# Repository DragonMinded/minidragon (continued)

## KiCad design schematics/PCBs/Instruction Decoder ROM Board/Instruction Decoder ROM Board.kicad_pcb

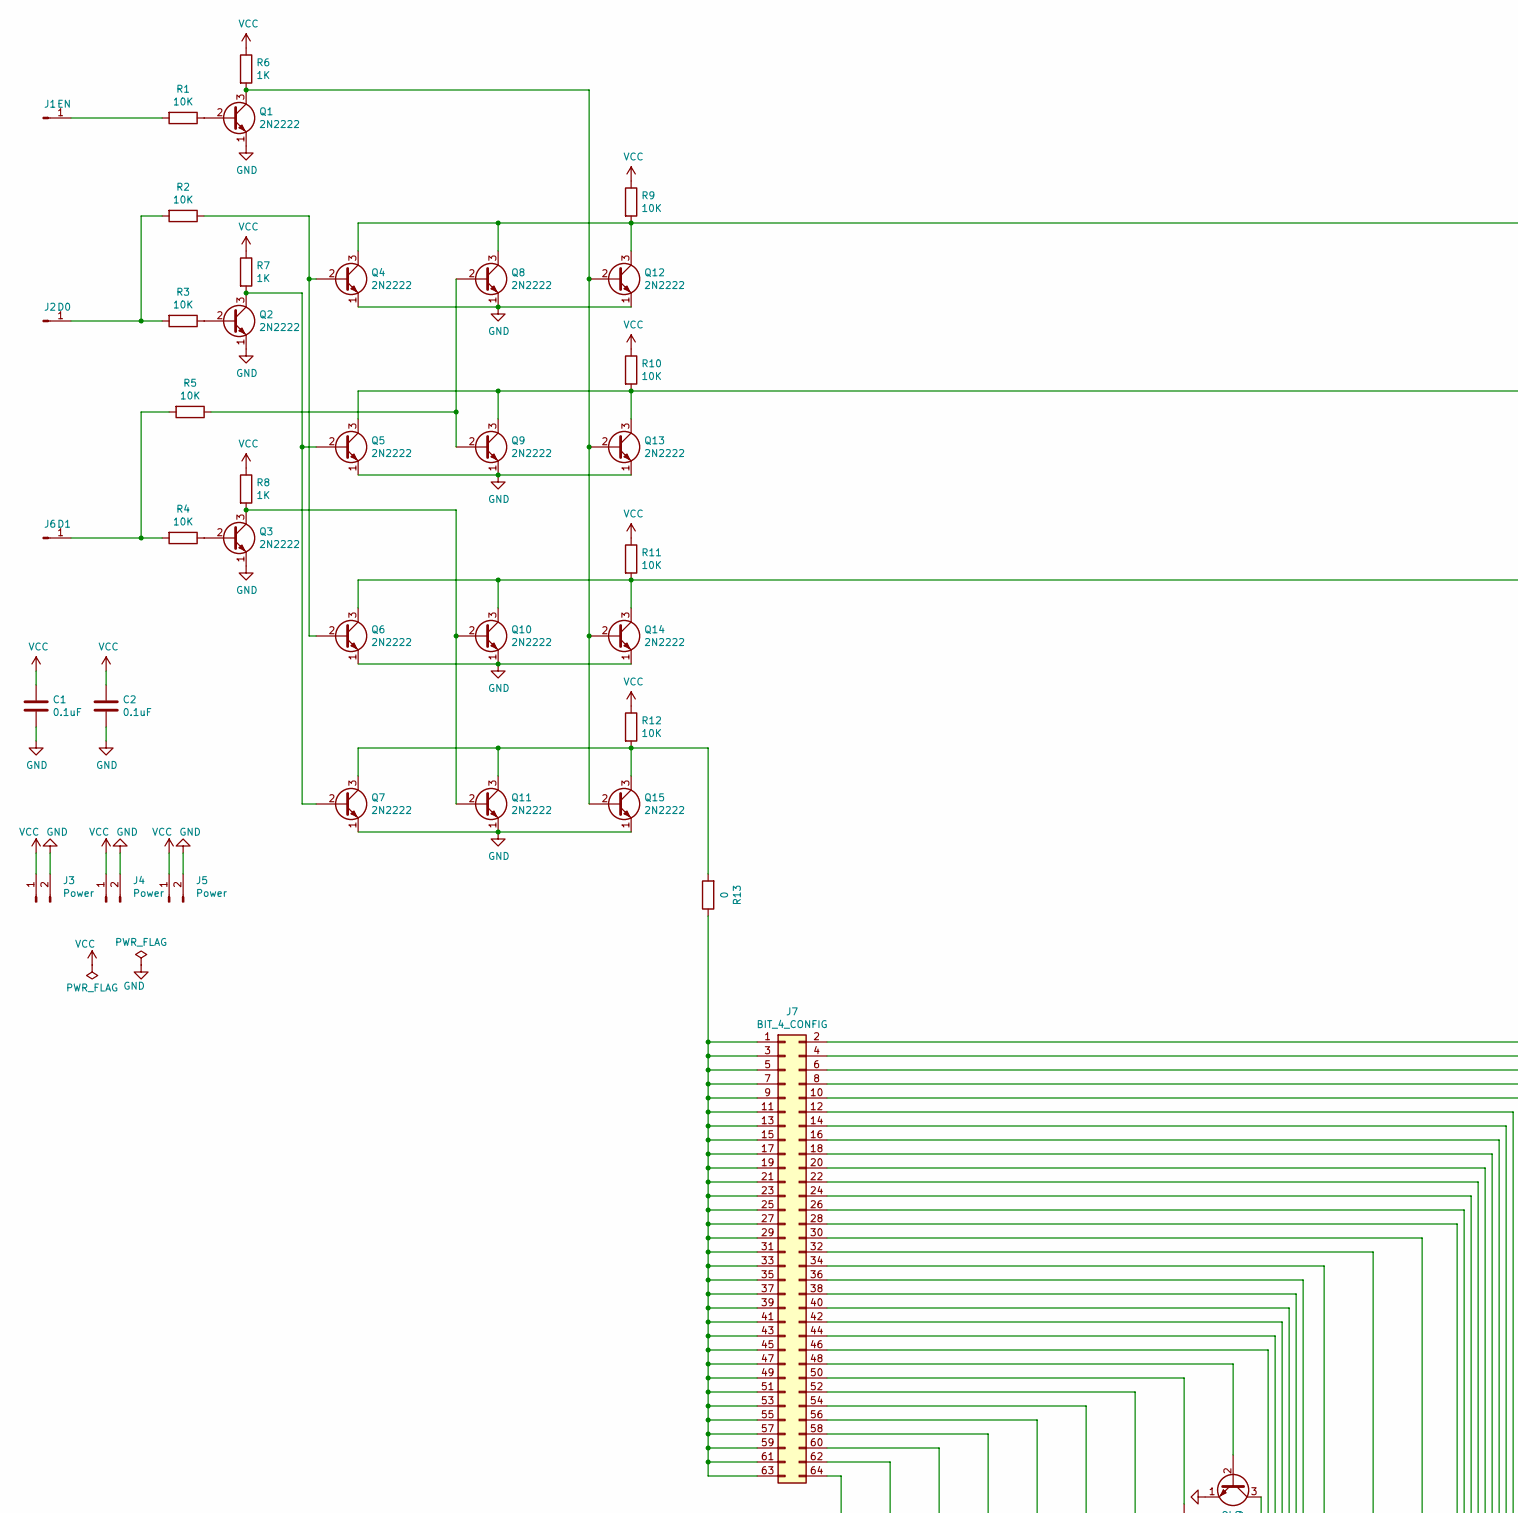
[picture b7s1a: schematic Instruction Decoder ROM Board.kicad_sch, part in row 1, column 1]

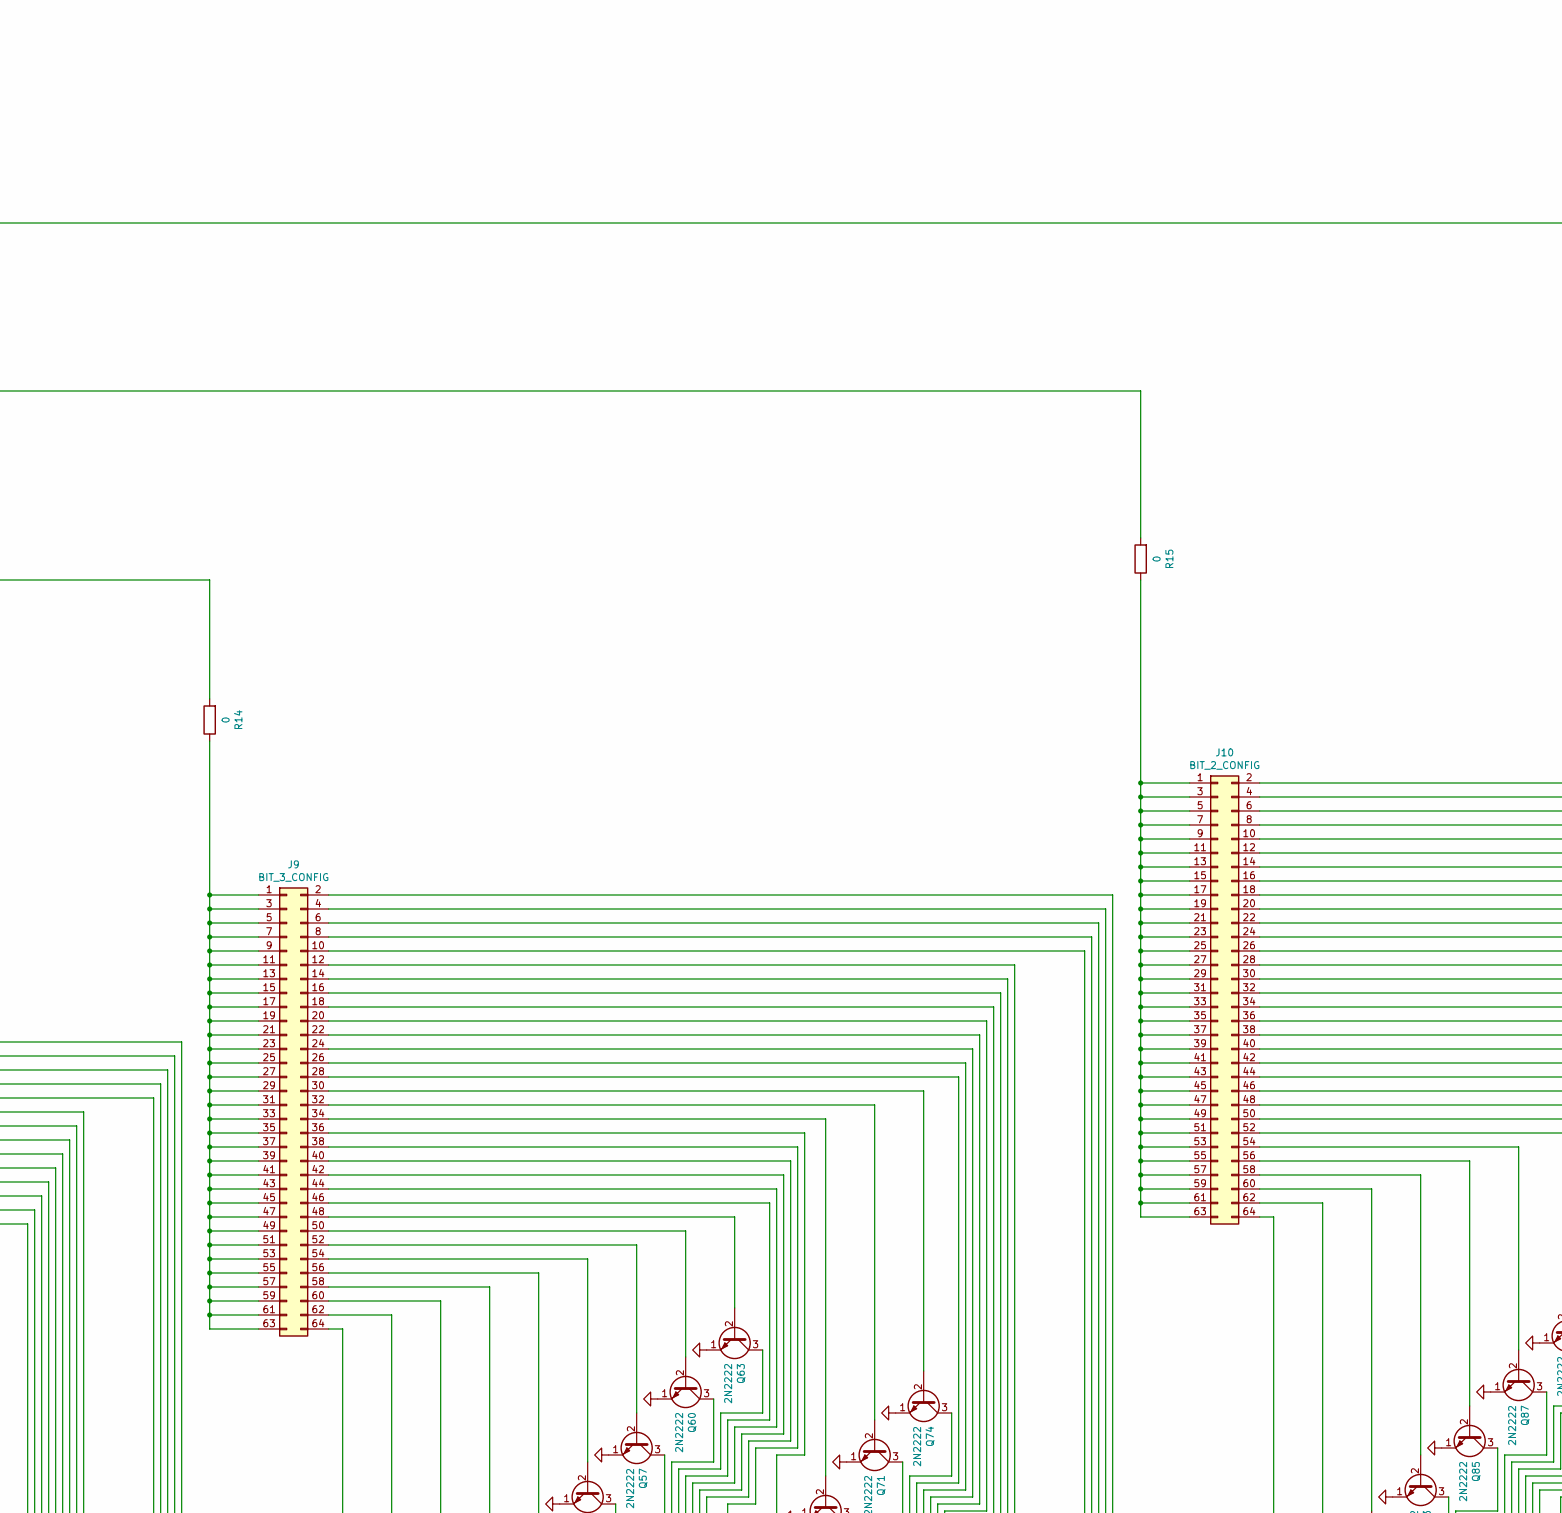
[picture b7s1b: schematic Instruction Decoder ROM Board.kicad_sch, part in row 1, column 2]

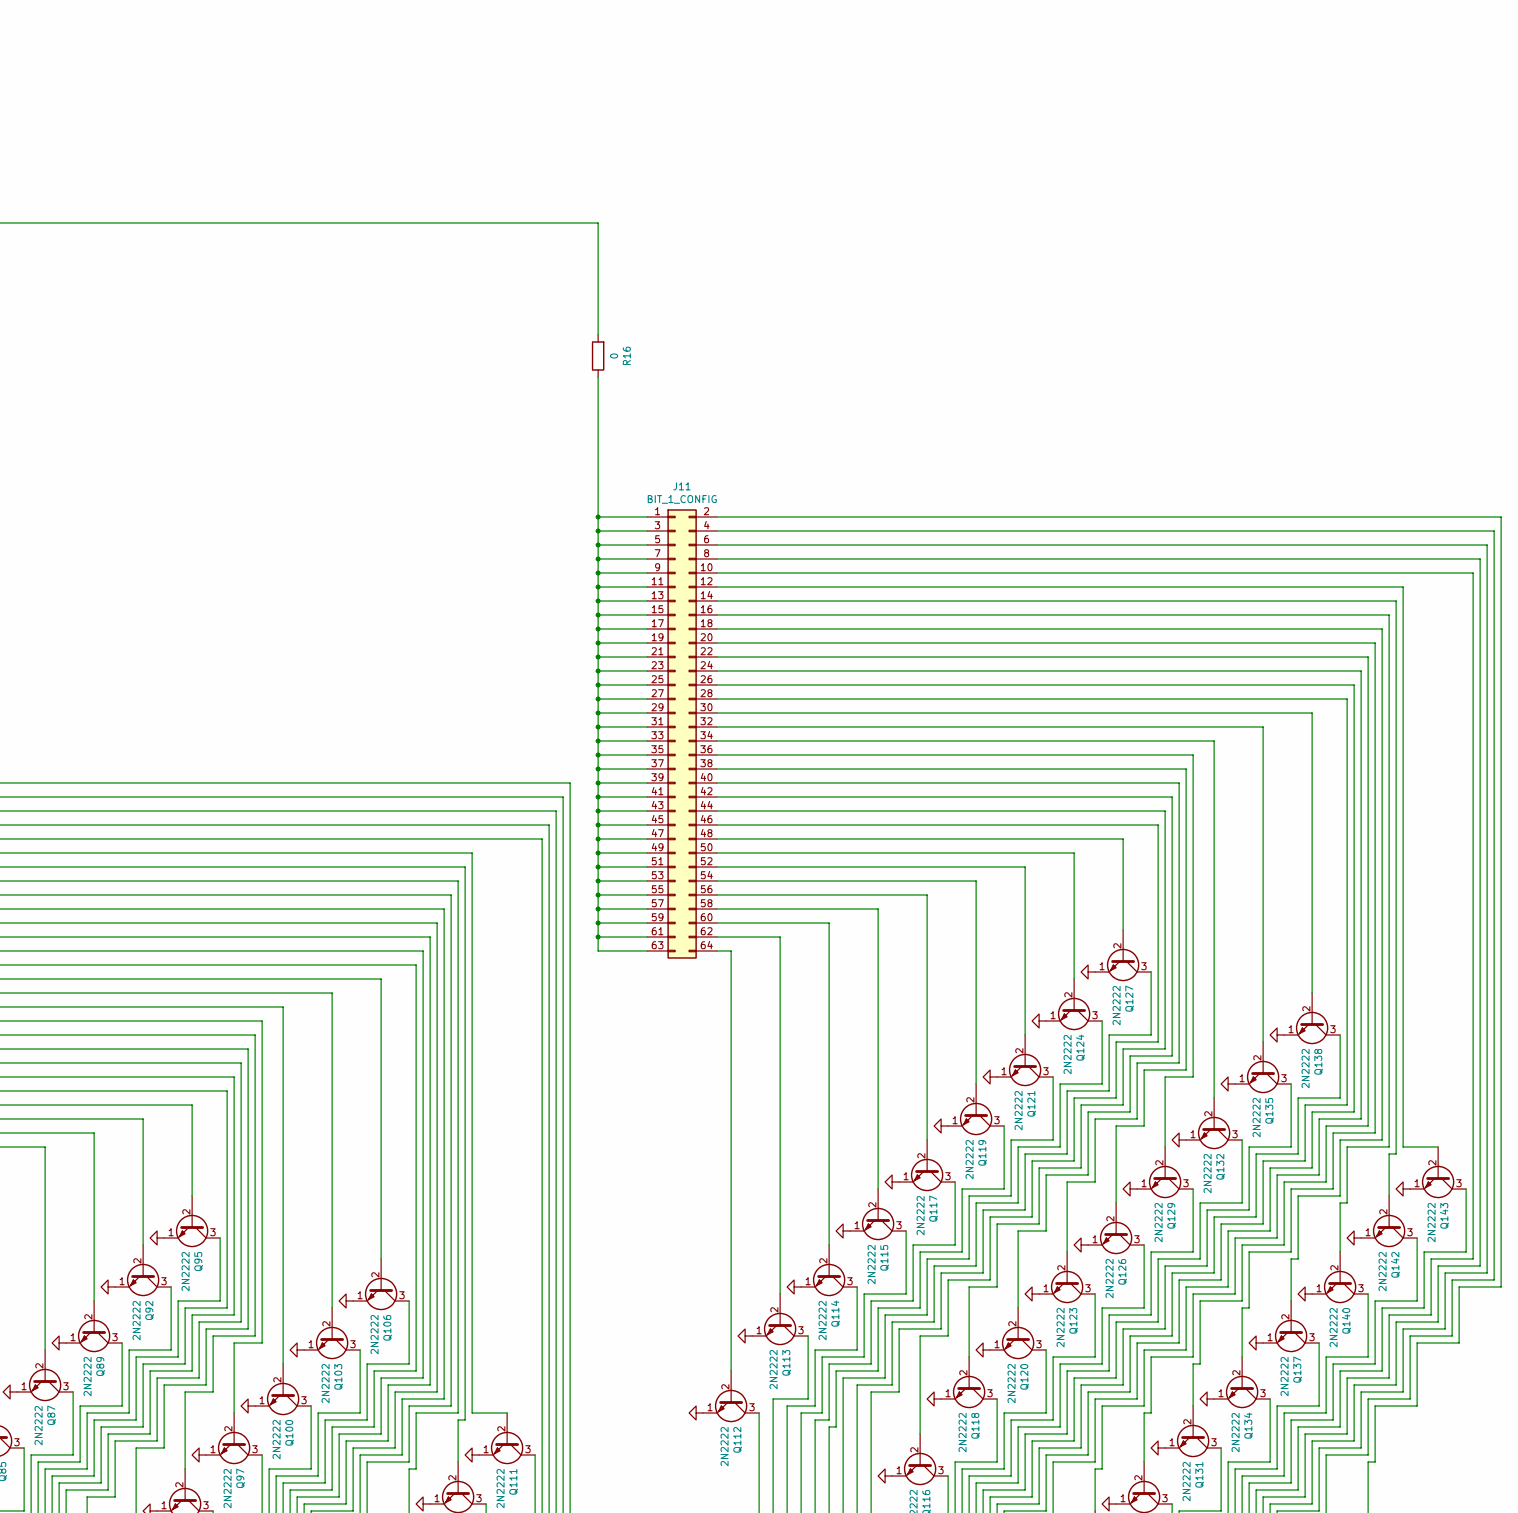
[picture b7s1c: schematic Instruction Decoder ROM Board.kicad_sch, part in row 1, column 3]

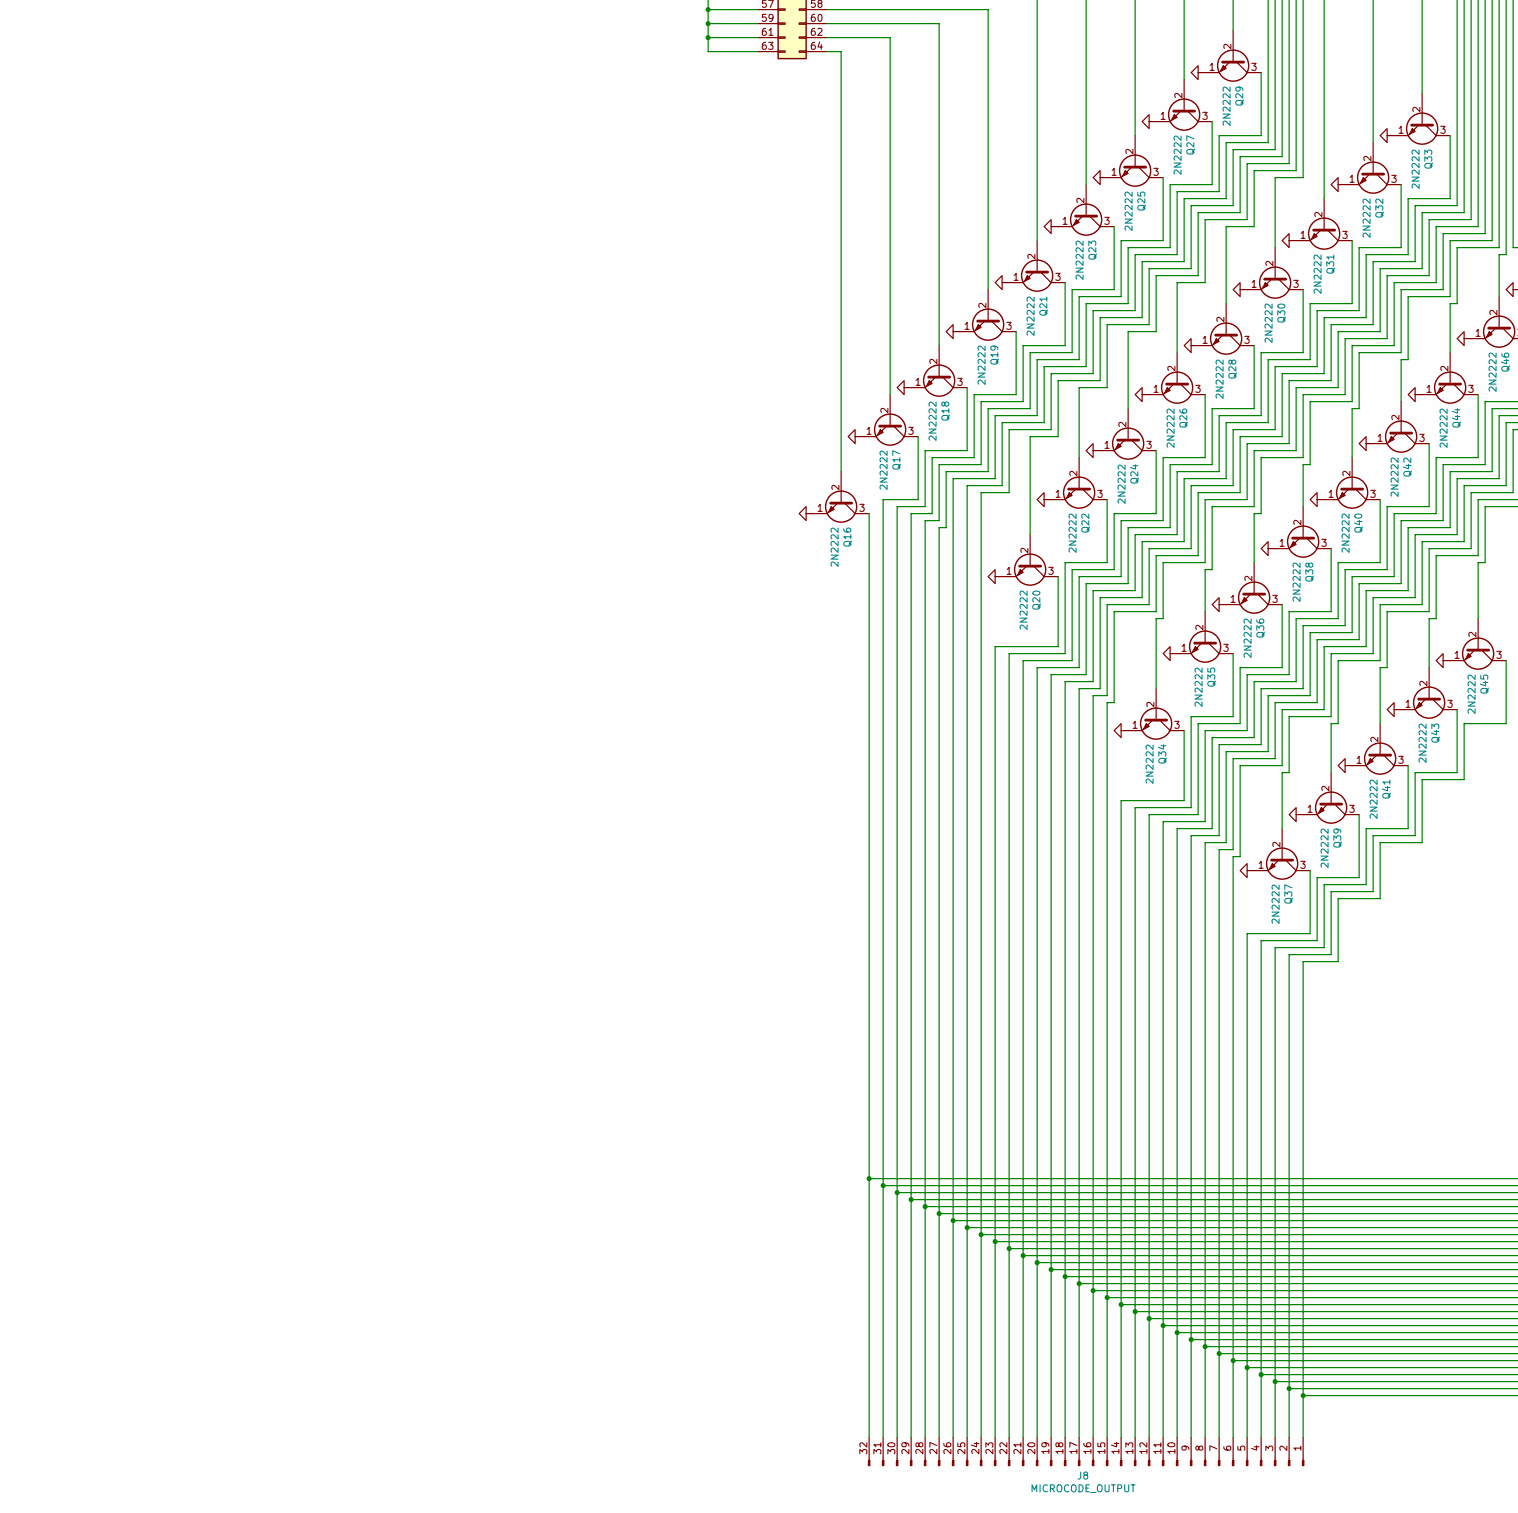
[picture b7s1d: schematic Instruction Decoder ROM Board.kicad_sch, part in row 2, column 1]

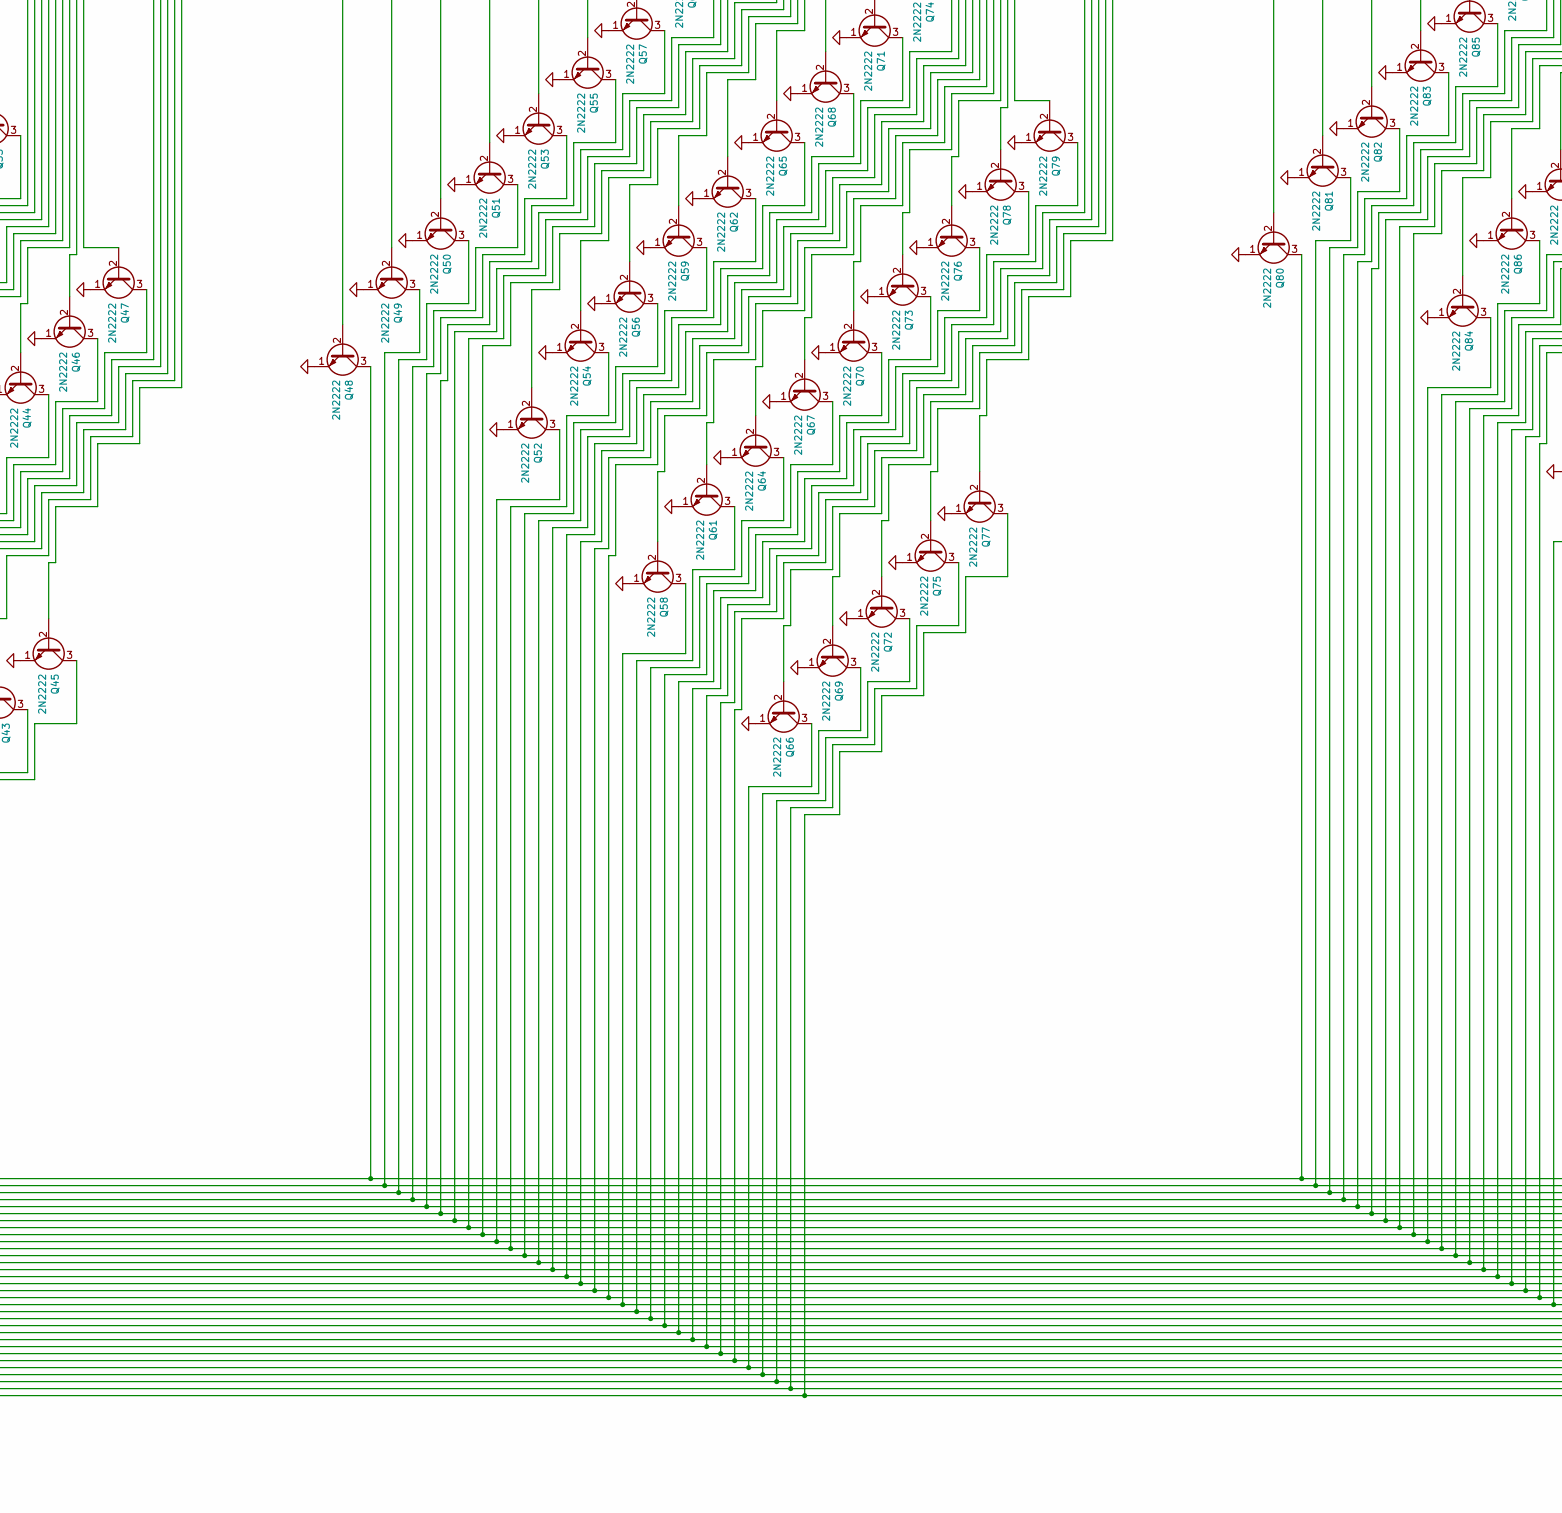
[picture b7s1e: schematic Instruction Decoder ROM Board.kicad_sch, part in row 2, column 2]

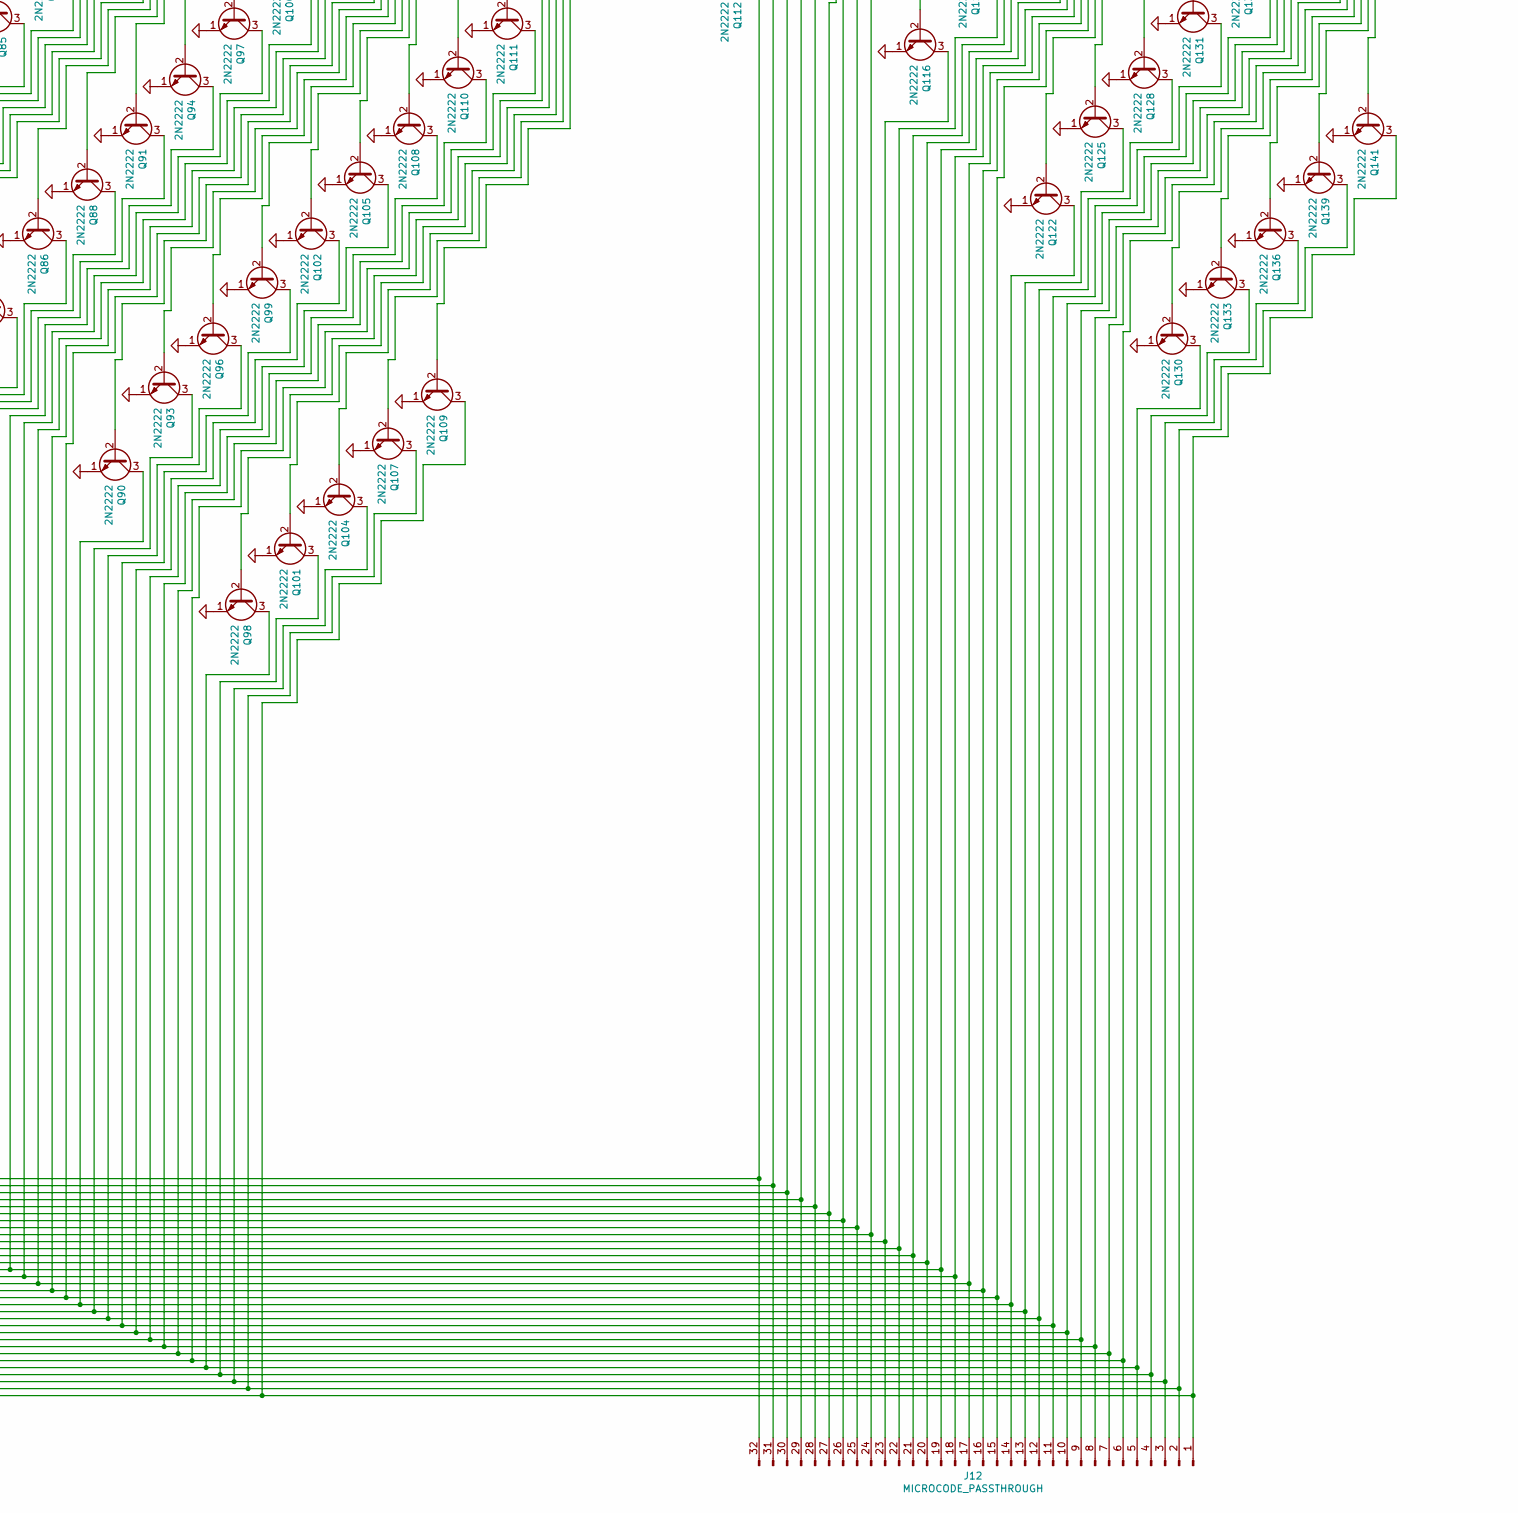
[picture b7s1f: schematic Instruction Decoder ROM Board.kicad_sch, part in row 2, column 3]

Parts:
C1, C2: 0.1uF; C_Disc_D4.3mm_W1.9mm_P5.00mm
J1: EN; PinHeader_1x01_P2.54mm_Vertical
J2: D0; PinHeader_1x01_P2.54mm_Vertical
J3, J4, J5: Power; PinHeader_1x02_P2.54mm_Vertical
J6: D1; PinHeader_1x01_P2.54mm_Vertical
J7: BIT_4_CONFIG; PinHeader_2x32_P2.54mm_Vertical
J8: MICROCODE_OUTPUT; PinHeader_1x32_P2.54mm_Vertical
J9: BIT_3_CONFIG; PinHeader_2x32_P2.54mm_Vertical
J10: BIT_2_CONFIG; PinHeader_2x32_P2.54mm_Vertical
J11: BIT_1_CONFIG; PinHeader_2x32_P2.54mm_Vertical
J12: MICROCODE_PASSTHROUGH; PinHeader_1x32_P2.54mm_Vertical
Q1, Q2, Q3, Q4, Q5, Q6, Q7, Q8, Q9, Q10, Q11, Q12, Q13, Q14, Q15, Q16, Q17, Q18, Q19, Q20, Q21, Q22, Q23, Q24, Q25, Q26, Q27, Q28, Q29, Q30, Q31, Q32, Q33, Q34, Q35, Q36, Q37, Q38, Q39, Q40, Q41, Q42, Q43, Q44, Q45, Q46, Q47, Q48, Q49, Q50, Q51, Q52, Q53, Q54, Q55, Q56, Q57, Q58, Q59, Q60, Q61, Q62, Q63, Q64, Q65, Q66, Q67, Q68, Q69, Q70, Q71, Q72, Q73, Q74, Q75, Q76, Q77, Q78, Q79, Q80, Q81, Q82, Q83, Q84, Q85, Q86, Q87, Q88, Q89, Q90, Q91, Q92, Q93, Q94, Q95, Q96, Q97, Q98, Q99, Q100, Q101, Q102, Q103, Q104, Q105, Q106, Q107, Q108, Q109, Q110, Q111, Q112, Q113, Q114, Q115, Q116, Q117, Q118, Q119, Q120, Q121, Q122, Q123, Q124, Q125, Q126, Q127, Q128, Q129, Q130, Q131, Q132, Q133, Q134, Q135, Q136, Q137, Q138, Q139, Q140, Q141, Q142, Q143: 2N2222; TO-92_Inline
R1, R2, R3, R4, R5, R9, R10, R11, R12: 10K; R_Axial_DIN0309_L9.0mm_D3.2mm_P12.70mm_Horizontal
R6, R7, R8: 1K; R_Axial_DIN0309_L9.0mm_D3.2mm_P12.70mm_Horizontal
R13, R14, R15, R16: 0; R_Axial_DIN0309_L9.0mm_D3.2mm_P12.70mm_Horizontal

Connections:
GND: C1.2, C2.2, J3.2, J4.2, J5.2, Q1.1 (E), Q2.1 (E), Q3.1 (E), Q4.1 (E), Q5.1 (E), Q6.1 (E), Q7.1 (E), Q8.1 (E), Q9.1 (E), Q10.1 (E), Q11.1 (E), Q12.1 (E), Q13.1 (E), Q14.1 (E), Q15.1 (E), Q16.1 (E), Q17.1 (E), Q18.1 (E), Q19.1 (E), Q20.1 (E), Q21.1 (E), Q22.1 (E), Q23.1 (E), Q24.1 (E), Q25.1 (E), Q26.1 (E), Q27.1 (E), Q28.1 (E), Q29.1 (E), Q30.1 (E), Q31.1 (E), Q32.1 (E), Q33.1 (E), Q34.1 (E), Q35.1 (E), Q36.1 (E), Q37.1 (E), Q38.1 (E), Q39.1 (E), Q40.1 (E), Q41.1 (E), Q42.1 (E), Q43.1 (E), Q44.1 (E), Q45.1 (E), Q46.1 (E), Q47.1 (E), Q48.1 (E), Q49.1 (E), Q50.1 (E), Q51.1 (E), Q52.1 (E), Q53.1 (E), Q54.1 (E), Q55.1 (E), Q56.1 (E), Q57.1 (E), Q58.1 (E), Q59.1 (E), Q60.1 (E), Q61.1 (E), Q62.1 (E), Q63.1 (E), Q64.1 (E), Q65.1 (E), Q66.1 (E), Q67.1 (E), Q68.1 (E), Q69.1 (E), Q70.1 (E), Q71.1 (E), Q72.1 (E), Q73.1 (E), Q74.1 (E), Q75.1 (E), Q76.1 (E), Q77.1 (E), Q78.1 (E), Q79.1 (E), Q80.1 (E), Q81.1 (E), Q82.1 (E), Q83.1 (E), Q84.1 (E), Q85.1 (E), Q86.1 (E), Q87.1 (E), Q88.1 (E), Q89.1 (E), Q90.1 (E), Q91.1 (E), Q92.1 (E), Q93.1 (E), Q94.1 (E), Q95.1 (E), Q96.1 (E), Q97.1 (E), Q98.1 (E), Q99.1 (E), Q100.1 (E), Q101.1 (E), Q102.1 (E), Q103.1 (E), Q104.1 (E), Q105.1 (E), Q106.1 (E), Q107.1 (E), Q108.1 (E), Q109.1 (E), Q110.1 (E), Q111.1 (E), Q112.1 (E), Q113.1 (E), Q114.1 (E), Q115.1 (E), Q116.1 (E), Q117.1 (E), Q118.1 (E), Q119.1 (E), Q120.1 (E), Q121.1 (E), Q122.1 (E), Q123.1 (E), Q124.1 (E), Q125.1 (E), Q126.1 (E), Q127.1 (E), Q128.1 (E), Q129.1 (E), Q130.1 (E), Q131.1 (E), Q132.1 (E), Q133.1 (E), Q134.1 (E), Q135.1 (E), Q136.1 (E), Q137.1 (E), Q138.1 (E), Q139.1 (E), Q140.1 (E), Q141.1 (E), Q142.1 (E), Q143.1 (E)
unnamed: J1.1, R1.2
unnamed: J2.1, R2.2, R3.2
unnamed: J6.1, R4.2, R5.2
unnamed: J7.1, J7.3, J7.5, J7.7, J7.9, J7.11, J7.13, J7.15, J7.17, J7.19, J7.21, J7.23, J7.25, J7.27, J7.29, J7.31, J7.33, J7.35, J7.37, J7.39, J7.41, J7.43, J7.45, J7.47, J7.49, J7.51, J7.53, J7.55, J7.57, J7.59, J7.61, J7.63, R13.1
unnamed: J7.2, Q45.2 (B)
unnamed: J7.4, Q43.2 (B)
unnamed: J7.6, Q41.2 (B)
unnamed: J7.8, Q39.2 (B)
unnamed: J7.10, Q37.2 (B)
unnamed: J7.12, Q47.2 (B)
unnamed: J7.14, Q46.2 (B)
unnamed: J7.16, Q44.2 (B)
unnamed: J7.18, Q42.2 (B)
unnamed: J7.20, Q40.2 (B)
unnamed: J7.22, Q38.2 (B)
unnamed: J7.24, Q36.2 (B)
unnamed: J7.26, Q35.2 (B)
unnamed: J7.28, Q34.2 (B)
unnamed: J7.30, Q33.2 (B)
unnamed: J7.32, Q32.2 (B)
unnamed: J7.34, Q31.2 (B)
unnamed: J7.36, Q30.2 (B)
unnamed: J7.38, Q28.2 (B)
unnamed: J7.40, Q26.2 (B)
unnamed: J7.42, Q24.2 (B)
unnamed: J7.44, Q22.2 (B)
unnamed: J7.46, Q20.2 (B)
unnamed: J7.48, Q29.2 (B)
unnamed: J7.50, Q27.2 (B)
unnamed: J7.52, Q25.2 (B)
unnamed: J7.54, Q23.2 (B)
unnamed: J7.56, Q21.2 (B)
unnamed: J7.58, Q19.2 (B)
unnamed: J7.60, Q18.2 (B)
unnamed: J7.62, Q17.2 (B)
unnamed: J7.64, Q16.2 (B)
unnamed: J9.1, J9.3, J9.5, J9.7, J9.9, J9.11, J9.13, J9.15, J9.17, J9.19, J9.21, J9.23, J9.25, J9.27, J9.29, J9.31, J9.33, J9.35, J9.37, J9.39, J9.41, J9.43, J9.45, J9.47, J9.49, J9.51, J9.53, J9.55, J9.57, J9.59, J9.61, J9.63, R14.1
unnamed: J9.2, Q77.2 (B)
unnamed: J9.4, Q75.2 (B)
unnamed: J9.6, Q72.2 (B)
unnamed: J9.8, Q69.2 (B)
unnamed: J9.10, Q66.2 (B)
unnamed: J9.12, Q79.2 (B)
unnamed: J9.14, Q78.2 (B)
unnamed: J9.16, Q76.2 (B)
unnamed: J9.18, Q73.2 (B)
unnamed: J9.20, Q70.2 (B)
unnamed: J9.22, Q67.2 (B)
unnamed: J9.24, Q64.2 (B)
unnamed: J9.26, Q61.2 (B)
unnamed: J9.28, Q58.2 (B)
unnamed: J9.30, Q74.2 (B)
unnamed: J9.32, Q71.2 (B)
unnamed: J9.34, Q68.2 (B)
unnamed: J9.36, Q65.2 (B)
unnamed: J9.38, Q62.2 (B)
unnamed: J9.40, Q59.2 (B)
unnamed: J9.42, Q56.2 (B)
unnamed: J9.44, Q54.2 (B)
unnamed: J9.46, Q52.2 (B)
unnamed: J9.48, Q63.2 (B)
unnamed: J9.50, Q60.2 (B)
unnamed: J9.52, Q57.2 (B)
unnamed: J9.54, Q55.2 (B)
unnamed: J9.56, Q53.2 (B)
unnamed: J9.58, Q51.2 (B)
unnamed: J9.60, Q50.2 (B)
unnamed: J9.62, Q49.2 (B)
unnamed: J9.64, Q48.2 (B)
unnamed: J10.1, J10.3, J10.5, J10.7, J10.9, J10.11, J10.13, J10.15, J10.17, J10.19, J10.21, J10.23, J10.25, J10.27, J10.29, J10.31, J10.33, J10.35, J10.37, J10.39, J10.41, J10.43, J10.45, J10.47, J10.49, J10.51, J10.53, J10.55, J10.57, J10.59, J10.61, J10.63, R15.1
unnamed: J10.2, Q109.2 (B)
unnamed: J10.4, Q107.2 (B)
unnamed: J10.6, Q104.2 (B)
unnamed: J10.8, Q101.2 (B)
unnamed: J10.10, Q98.2 (B)
unnamed: J10.12, Q111.2 (B)
unnamed: J10.14, Q110.2 (B)
unnamed: J10.16, Q108.2 (B)
unnamed: J10.18, Q105.2 (B)
unnamed: J10.20, Q102.2 (B)
unnamed: J10.22, Q99.2 (B)
unnamed: J10.24, Q96.2 (B)
unnamed: J10.26, Q93.2 (B)
unnamed: J10.28, Q90.2 (B)
unnamed: J10.30, Q106.2 (B)
unnamed: J10.32, Q103.2 (B)
unnamed: J10.34, Q100.2 (B)
unnamed: J10.36, Q97.2 (B)
unnamed: J10.38, Q94.2 (B)
unnamed: J10.40, Q91.2 (B)
unnamed: J10.42, Q88.2 (B)
unnamed: J10.44, Q86.2 (B)
unnamed: J10.46, Q84.2 (B)
unnamed: J10.48, Q95.2 (B)
unnamed: J10.50, Q92.2 (B)
unnamed: J10.52, Q89.2 (B)
unnamed: J10.54, Q87.2 (B)
unnamed: J10.56, Q85.2 (B)
unnamed: J10.58, Q83.2 (B)
unnamed: J10.60, Q82.2 (B)
unnamed: J10.62, Q81.2 (B)
unnamed: J10.64, Q80.2 (B)
unnamed: J11.1, J11.3, J11.5, J11.7, J11.9, J11.11, J11.13, J11.15, J11.17, J11.19, J11.21, J11.23, J11.25, J11.27, J11.29, J11.31, J11.33, J11.35, J11.37, J11.39, J11.41, J11.43, J11.45, J11.47, J11.49, J11.51, J11.53, J11.55, J11.57, J11.59, J11.61, J11.63, R16.1
unnamed: J11.2, Q141.2 (B)
unnamed: J11.4, Q139.2 (B)
unnamed: J11.6, Q136.2 (B)
unnamed: J11.8, Q133.2 (B)
unnamed: J11.10, Q130.2 (B)
unnamed: J11.12, Q143.2 (B)
unnamed: J11.14, Q142.2 (B)
unnamed: J11.16, Q140.2 (B)
unnamed: J11.18, Q137.2 (B)
unnamed: J11.20, Q134.2 (B)
unnamed: J11.22, Q131.2 (B)
unnamed: J11.24, Q128.2 (B)
unnamed: J11.26, Q125.2 (B)
unnamed: J11.28, Q122.2 (B)
unnamed: J11.30, Q138.2 (B)
unnamed: J11.32, Q135.2 (B)
unnamed: J11.34, Q132.2 (B)
unnamed: J11.36, Q129.2 (B)
unnamed: J11.38, Q126.2 (B)
unnamed: J11.40, Q123.2 (B)
unnamed: J11.42, Q120.2 (B)
unnamed: J11.44, Q118.2 (B)
unnamed: J11.46, Q116.2 (B)
unnamed: J11.48, Q127.2 (B)
unnamed: J11.50, Q124.2 (B)
unnamed: J11.52, Q121.2 (B)
unnamed: J11.54, Q119.2 (B)
unnamed: J11.56, Q117.2 (B)
unnamed: J11.58, Q115.2 (B)
unnamed: J11.60, Q114.2 (B)
unnamed: J11.62, Q113.2 (B)
unnamed: J11.64, Q112.2 (B)
unnamed: J8.1, J12.1, Q45.3 (C), Q77.3 (C), Q109.3 (C), Q141.3 (C)
unnamed: J8.2, J12.2, Q43.3 (C), Q75.3 (C), Q107.3 (C), Q139.3 (C)
unnamed: J8.3, J12.3, Q41.3 (C), Q72.3 (C), Q104.3 (C), Q136.3 (C)
unnamed: J8.4, J12.4, Q39.3 (C), Q69.3 (C), Q101.3 (C), Q133.3 (C)
unnamed: J8.5, J12.5, Q37.3 (C), Q66.3 (C), Q98.3 (C), Q130.3 (C)
unnamed: J8.6, J12.6, Q47.3 (C), Q79.3 (C), Q111.3 (C), Q143.3 (C)
unnamed: J8.7, J12.7, Q46.3 (C), Q78.3 (C), Q110.3 (C), Q142.3 (C)
unnamed: J8.8, J12.8, Q44.3 (C), Q76.3 (C), Q108.3 (C), Q140.3 (C)
unnamed: J8.9, J12.9, Q42.3 (C), Q73.3 (C), Q105.3 (C), Q137.3 (C)
unnamed: J8.10, J12.10, Q40.3 (C), Q70.3 (C), Q102.3 (C), Q134.3 (C)
unnamed: J8.11, J12.11, Q38.3 (C), Q67.3 (C), Q99.3 (C), Q131.3 (C)
unnamed: J8.12, J12.12, Q36.3 (C), Q64.3 (C), Q96.3 (C), Q128.3 (C)
unnamed: J8.13, J12.13, Q35.3 (C), Q61.3 (C), Q93.3 (C), Q125.3 (C)
unnamed: J8.14, J12.14, Q34.3 (C), Q58.3 (C), Q90.3 (C), Q122.3 (C)
unnamed: J8.15, J12.15, Q33.3 (C), Q74.3 (C), Q106.3 (C), Q138.3 (C)
unnamed: J8.16, J12.16, Q32.3 (C), Q71.3 (C), Q103.3 (C), Q135.3 (C)
unnamed: J8.17, J12.17, Q31.3 (C), Q68.3 (C), Q100.3 (C), Q132.3 (C)
unnamed: J8.18, J12.18, Q30.3 (C), Q65.3 (C), Q97.3 (C), Q129.3 (C)
unnamed: J8.19, J12.19, Q28.3 (C), Q62.3 (C), Q94.3 (C), Q126.3 (C)
unnamed: J8.20, J12.20, Q26.3 (C), Q59.3 (C), Q91.3 (C), Q123.3 (C)
unnamed: J8.21, J12.21, Q24.3 (C), Q56.3 (C), Q88.3 (C), Q120.3 (C)
unnamed: J8.22, J12.22, Q22.3 (C), Q54.3 (C), Q86.3 (C), Q118.3 (C)
unnamed: J8.23, J12.23, Q20.3 (C), Q52.3 (C), Q84.3 (C), Q116.3 (C)
unnamed: J8.24, J12.24, Q29.3 (C), Q63.3 (C), Q95.3 (C), Q127.3 (C)
unnamed: J8.25, J12.25, Q27.3 (C), Q60.3 (C), Q92.3 (C), Q124.3 (C)
unnamed: J8.26, J12.26, Q25.3 (C), Q57.3 (C), Q89.3 (C), Q121.3 (C)
unnamed: J8.27, J12.27, Q23.3 (C), Q55.3 (C), Q87.3 (C), Q119.3 (C)
unnamed: J8.28, J12.28, Q21.3 (C), Q53.3 (C), Q85.3 (C), Q117.3 (C)
unnamed: J8.29, J12.29, Q19.3 (C), Q51.3 (C), Q83.3 (C), Q115.3 (C)
unnamed: J8.30, J12.30, Q18.3 (C), Q50.3 (C), Q82.3 (C), Q114.3 (C)
unnamed: J8.31, J12.31, Q17.3 (C), Q49.3 (C), Q81.3 (C), Q113.3 (C)
unnamed: J8.32, J12.32, Q16.3 (C), Q48.3 (C), Q80.3 (C), Q112.3 (C)
unnamed: Q1.2 (B), R1.1
unnamed: Q1.3 (C), Q12.2 (B), Q13.2 (B), Q14.2 (B), Q15.2 (B), R6.2
unnamed: Q2.2 (B), R3.1
unnamed: Q2.3 (C), Q5.2 (B), Q7.2 (B), R7.2
unnamed: Q3.2 (B), R4.1
unnamed: Q4.2 (B), Q6.2 (B), R2.1
unnamed: Q8.2 (B), Q9.2 (B), R5.1
unnamed: Q3.3 (C), Q10.2 (B), Q11.2 (B), R8.2
unnamed: Q6.3 (C), Q10.3 (C), Q14.3 (C), R11.2, R14.2
unnamed: Q7.3 (C), Q11.3 (C), Q15.3 (C), R12.2, R13.2
unnamed: Q4.3 (C), Q8.3 (C), Q12.3 (C), R9.2, R16.2
unnamed: Q5.3 (C), Q9.3 (C), Q13.3 (C), R10.2, R15.2
VCC: C1.1, C2.1, J3.1, J4.1, J5.1, R6.1, R7.1, R8.1, R9.1, R10.1, R11.1, R12.1

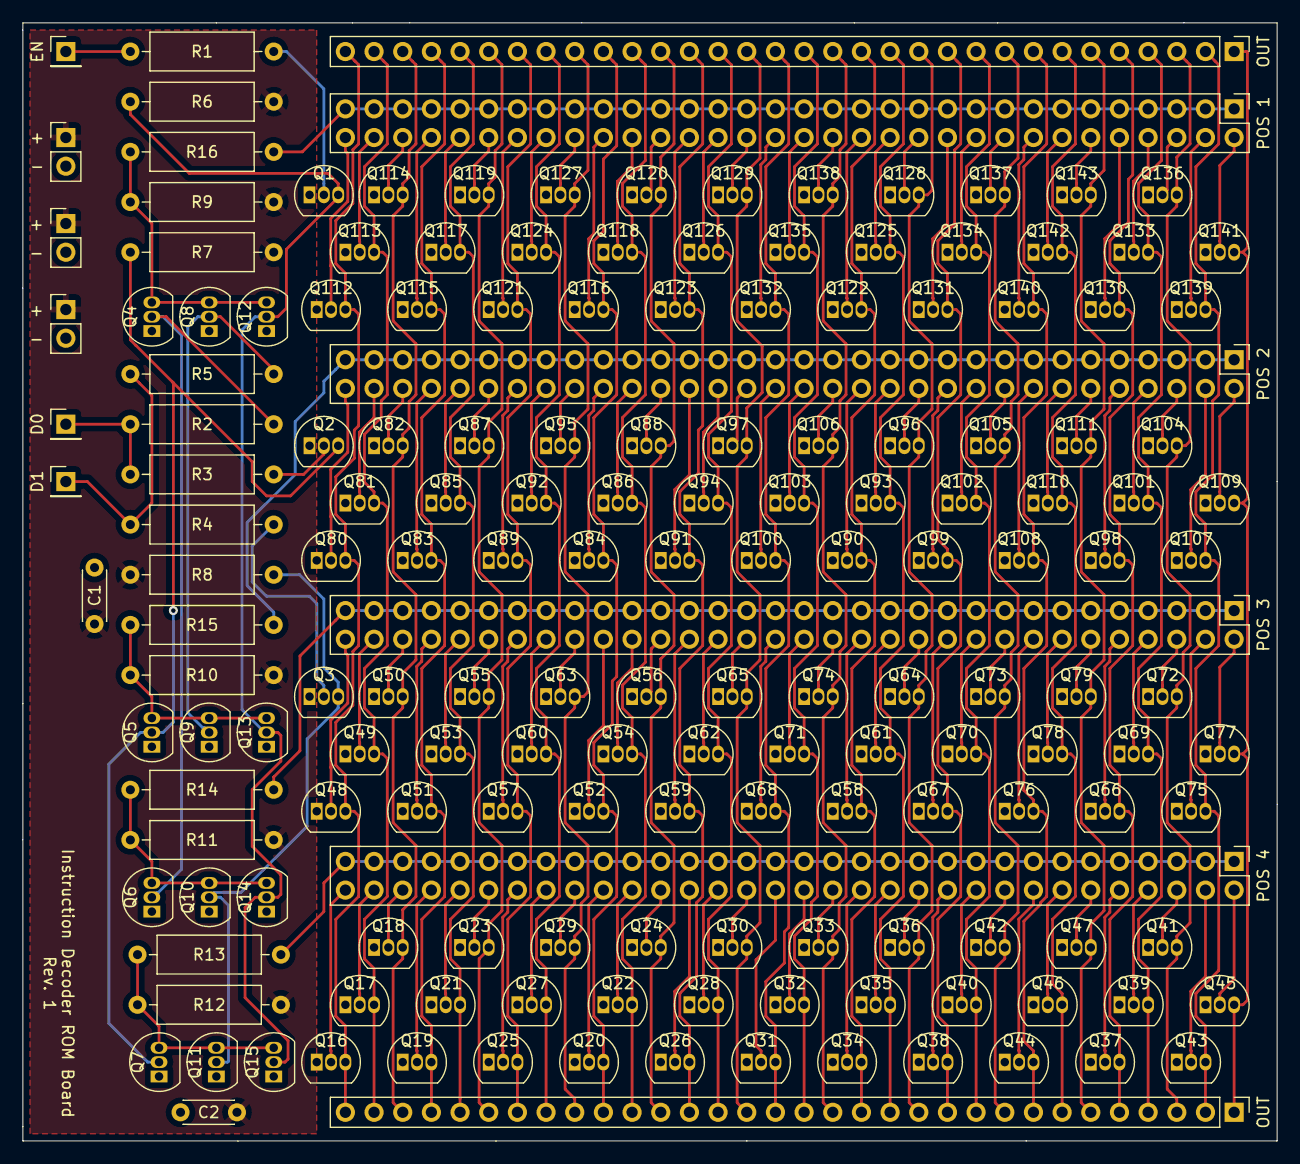
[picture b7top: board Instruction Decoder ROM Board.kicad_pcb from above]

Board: 2 copper layers, 111.1 x 99.1 mm, 173 parts (0 on the bottom side), 181 nets.

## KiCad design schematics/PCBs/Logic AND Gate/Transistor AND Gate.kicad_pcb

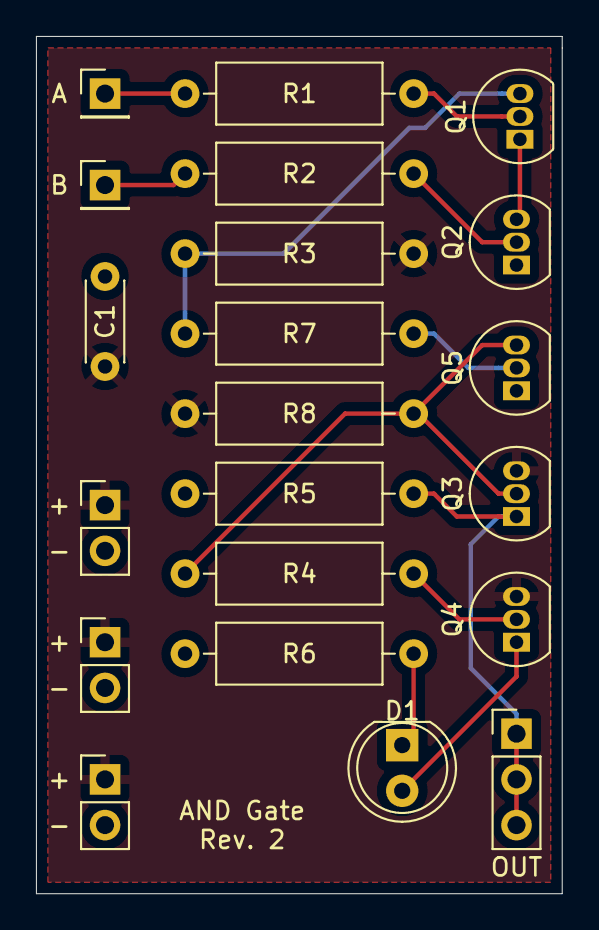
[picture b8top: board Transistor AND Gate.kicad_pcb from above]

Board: 2 copper layers, 29.2 x 47.6 mm, 21 parts (0 on the bottom side), 14 nets.

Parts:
C1: 0.1uF; C_Disc_D4.3mm_W1.9mm_P5.00mm
D1: RED; LED_D5.0mm
J1, J4, J5: Power; PinHeader_1x02_P2.54mm_Vertical
J2: A; PinHeader_1x01_P2.54mm_Vertical
J3: B; PinHeader_1x01_P2.54mm_Vertical
J6: OUT; PinHeader_1x03_P2.54mm_Vertical
Q1, Q2, Q3, Q4, Q5: 2N2222; TO-92_Inline
R1, R2, R4, R7: 10K; R_Axial_DIN0309_L9.0mm_D3.2mm_P12.70mm_Horizontal
R3, R5, R6, R8: 1K; R_Axial_DIN0309_L9.0mm_D3.2mm_P12.70mm_Horizontal

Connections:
GND: C1.2, J1.2, J4.2, J5.2, Q2.1 (E), Q5.1 (E), R5.2, R6.1
unnamed: D1.2 (A), Q4.1 (E)
unnamed: D1.1 (K), R6.2
unnamed: J2.1, R1.2
unnamed: J3.1, R2.2
unnamed: J6.1, J6.2, J6.3, Q3.1 (E), R5.1
unnamed: Q1.2 (B), R1.1
unnamed: Q1.3 (C), R3.2, R7.2
unnamed: Q1.1 (E), Q2.3 (C)
unnamed: Q2.2 (B), R2.1
unnamed: Q3.2 (B), Q5.3 (C), R4.2, R8.2
unnamed: Q4.2 (B), R4.1
unnamed: Q5.2 (B), R7.1
VCC: C1.1, J1.1, J4.1, J5.1, Q3.3 (C), Q4.3 (C), R3.1, R8.1
